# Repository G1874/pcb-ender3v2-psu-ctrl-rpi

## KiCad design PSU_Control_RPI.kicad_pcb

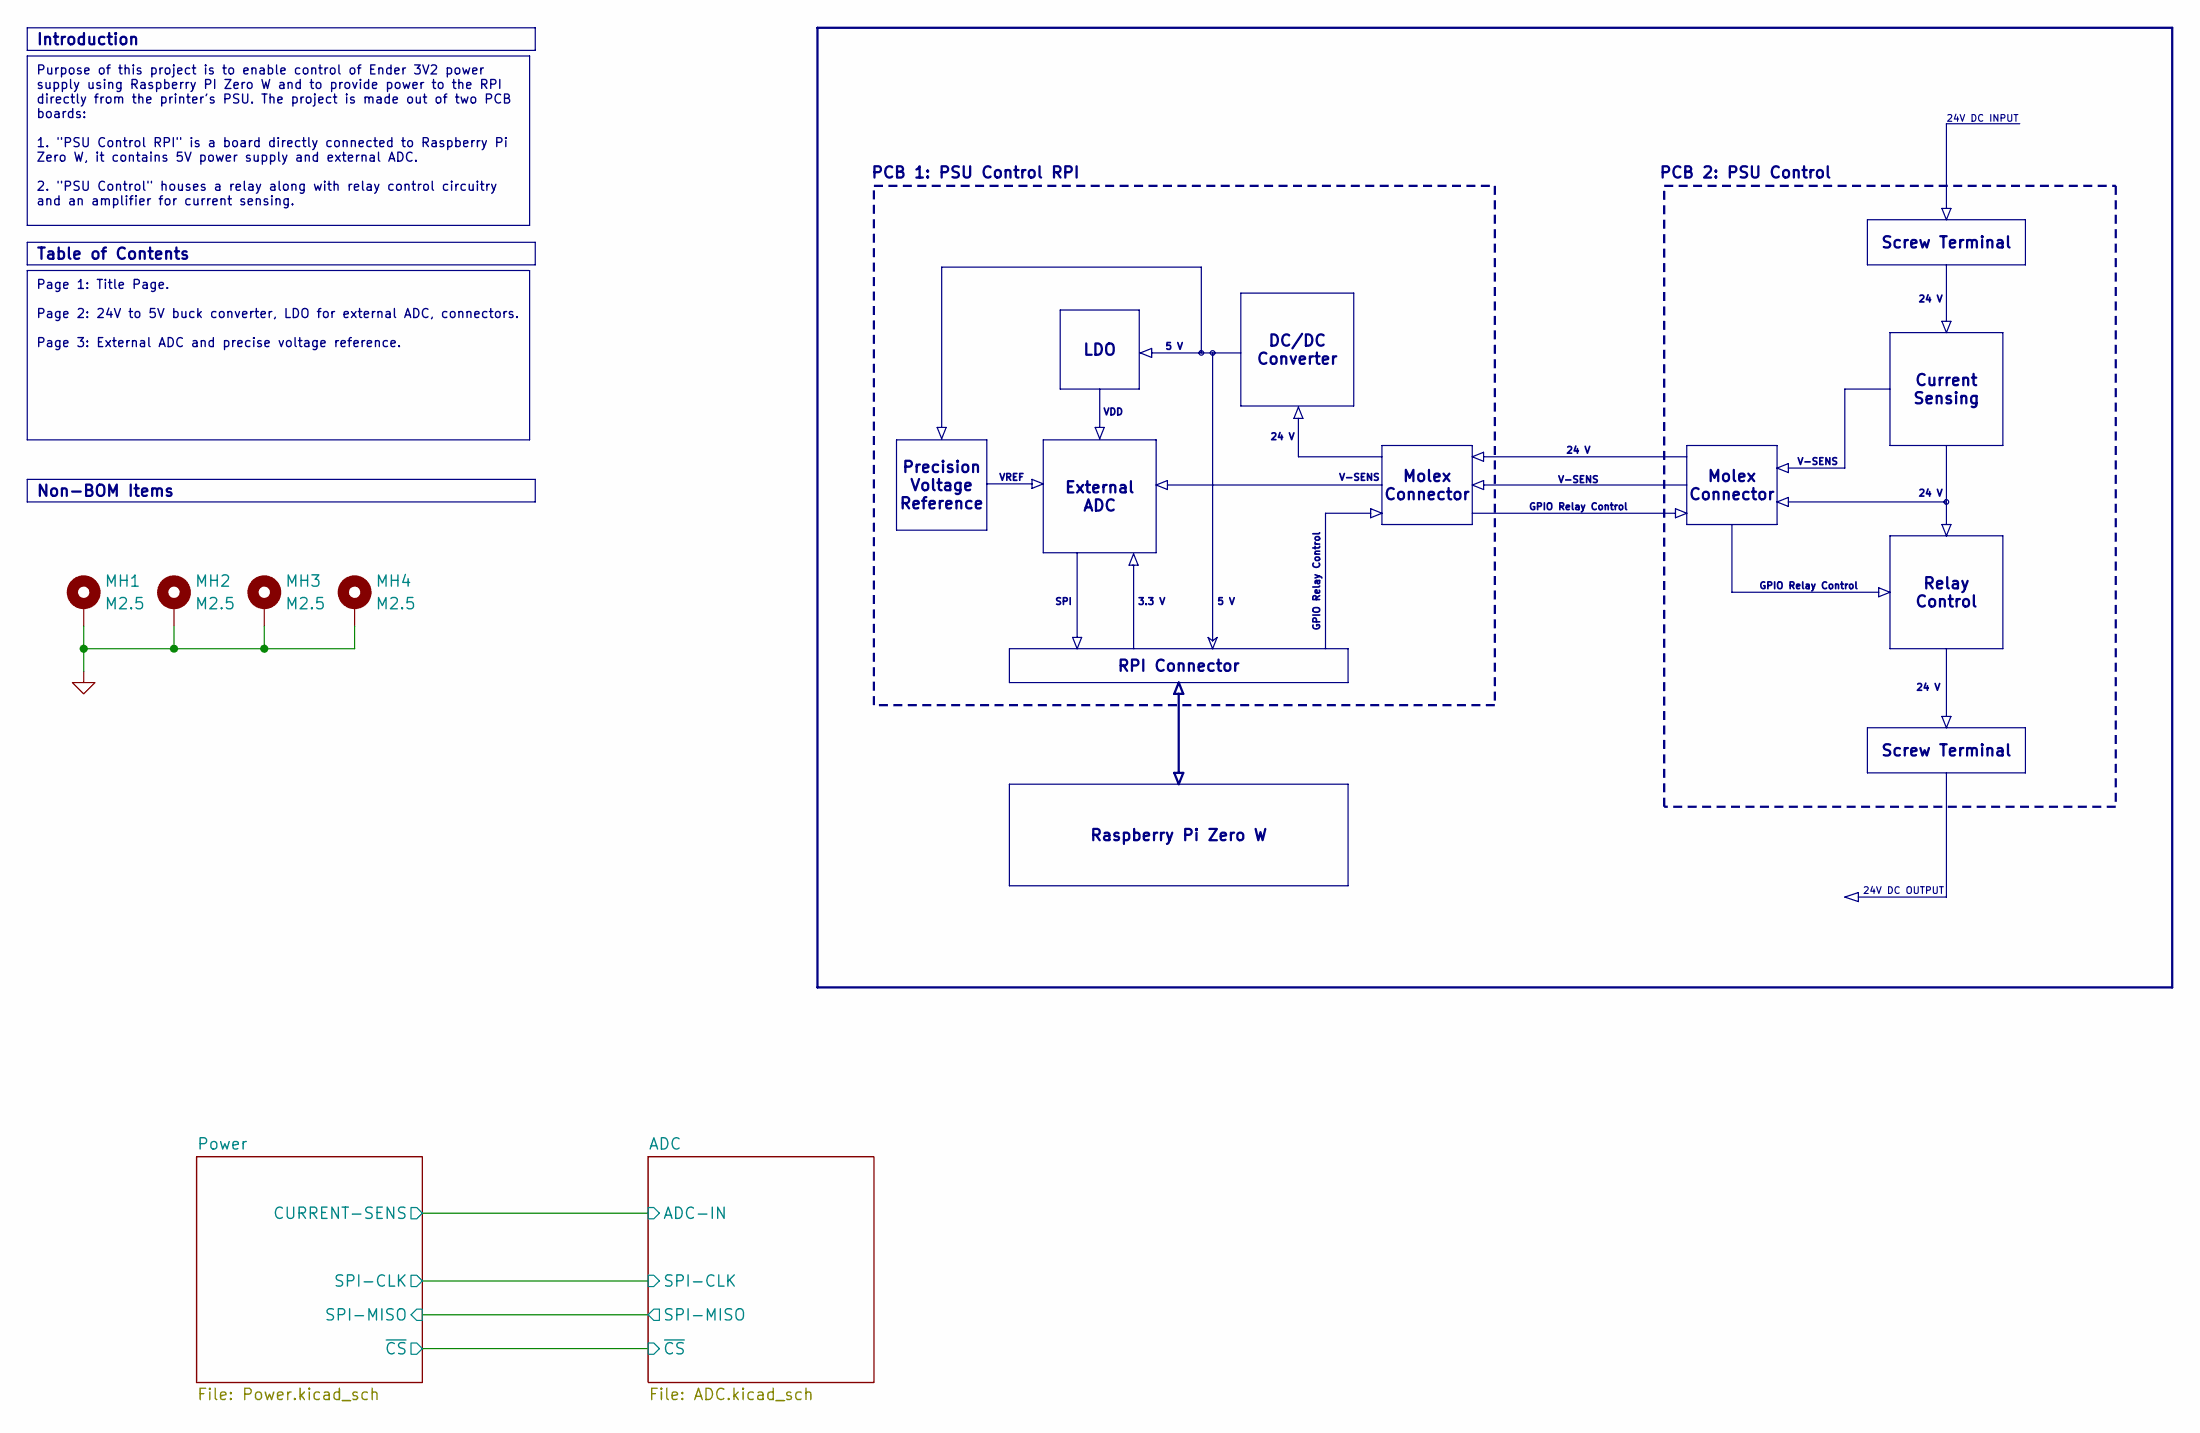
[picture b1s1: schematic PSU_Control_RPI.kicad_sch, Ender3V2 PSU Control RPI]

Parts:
MH1, MH2, MH3, MH4: M2.5; MountingHole_2.7mm_M2.5_ISO14580_Pad_TopOnly

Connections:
GND: MH1.1, MH2.1, MH3.1, MH4.1; also elsewhere on the board

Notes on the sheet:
24 V
PCB 1: PSU Control RPI
V-SENS
3.3 V
24V DC INPUT
GPIO Relay Control
SPI
VREF
VDD
5 V
PCB 2: PSU Control
24V DC OUTPUT
LDO
External ADC
Introduction
Molex Connector
Raspberry Pi Zero W
Screw Terminal
Relay Control
Non-BOM Items
Page 1: Title Page. Page 2: 24V to 5V buck converter, LDO for external ADC, connectors. Page 3: External ADC and precise voltage reference.
Current Sensing
Purpose of this project is to enable control of Ender 3V2 power supply using Raspberry PI Zero W and to provide power to the RPI directly from the printer's PSU. The project is made out of two PCB boards: 1. "PSU Control RPI" is a board directly connected to Raspberry Pi Zero W, it contains 5V powe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
Table of Contents
Precision Voltage Reference
RPI Connector
DC/DC Converter

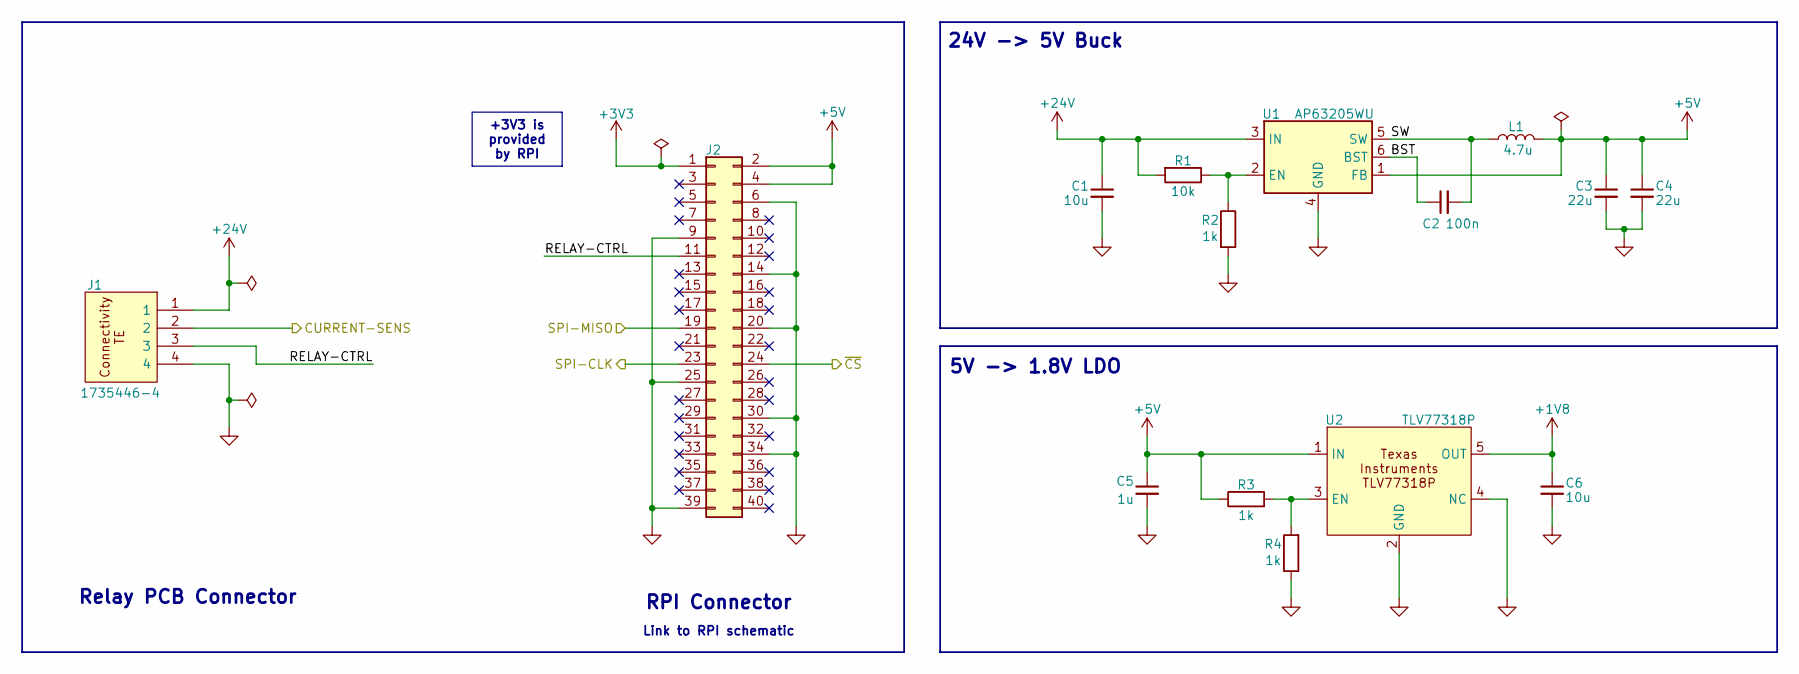
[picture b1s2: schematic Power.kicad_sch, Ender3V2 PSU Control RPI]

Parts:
C1, C6: 10u; C_1206_3216Metric_Pad1.33x1.80mm_HandSolder; Manufacturer Part Number CL31A106KBHNNNE
C2: 100n; C_0402_1005Metric_Pad0.74x0.62mm_HandSolder; Manufacturer Part Number GRM155R61H104KE19D
C3, C4: 22u; C_1206_3216Metric_Pad1.33x1.80mm_HandSolder; Manufacturer Part Number CL31A226KAHNNNE
C5: 1u; C_0603_1608Metric_Pad1.08x0.95mm_HandSolder; Manufacturer Part Number MCASL168SB7105KTNA01
J1: 1735446-4; SHDR4W60P0X200_1X4_1000X520X637P; Manufacturer Part Number 1735446-4
J2: 61304021821; Manufacturer Part Number 61304021821
L1: 4.7u; L_1008_2520Metric_Pad1.43x2.20mm_HandSolder; Manufacturer Part Number LCENA2520MKT4R7M0NK
R1: 10k; R_0603_1608Metric_Pad0.98x0.95mm_HandSolder; Manufacturer Part Number WCR-WCR0603LF-1002-F-P-LT
R2, R3, R4: 1k; R_0805_2012Metric_Pad1.20x1.40mm_HandSolder; Manufacturer Part Number ERA-6AEB102V
U1: AP63205WU; TSOT-23-6_HandSoldering; Manufacturer Part Number AP63205WU
U2: TLV77318P; SOT-23-5_HandSoldering; Manufacturer Part Number TLV77318P

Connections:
+1V8: C6.1, U2.5 (OUT); also elsewhere on the board
+3V3: J2.1; also elsewhere on the board
+5V: C3.1, C4.1, C5.1, J2.2, J2.4, L1.2, R3.1, U1.1 (FB), U2.1 (IN); also elsewhere on the board
+24V: C1.1, J1.1, R1.2, U1.3 (IN)
/ADC/ADC-IN: J1.2; also elsewhere on the board
/ADC/SPI-CLK: J2.23; also elsewhere on the board
/ADC/SPI-MISO: J2.19; also elsewhere on the board
/ADC/~CS: J2.24; also elsewhere on the board
/Power/BST: C2.1, U1.6 (BST)
/Power/RELAY-CTRL: J1.3, J2.11
/Power/SW: C2.2, L1.1, U1.5 (SW)
GND: C1.2, C3.2, C4.2, C5.2, C6.2, J1.4, J2.6, J2.9, J2.14, J2.20, J2.25, J2.30, J2.34, J2.39, R2.2, R4.1, U1.4 (GND), U2.2 (GND), U2.4 (NC); also elsewhere on the board
unnamed: R1.1, R2.1, U1.2 (EN)
unnamed: R3.2, R4.2, U2.3 (EN)

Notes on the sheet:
RPI Connector
Relay PCB Connector
24V -> 5V Buck
Link to RPI schematic
5V -> 1.8V LDO
+3V3 is provided by RPI

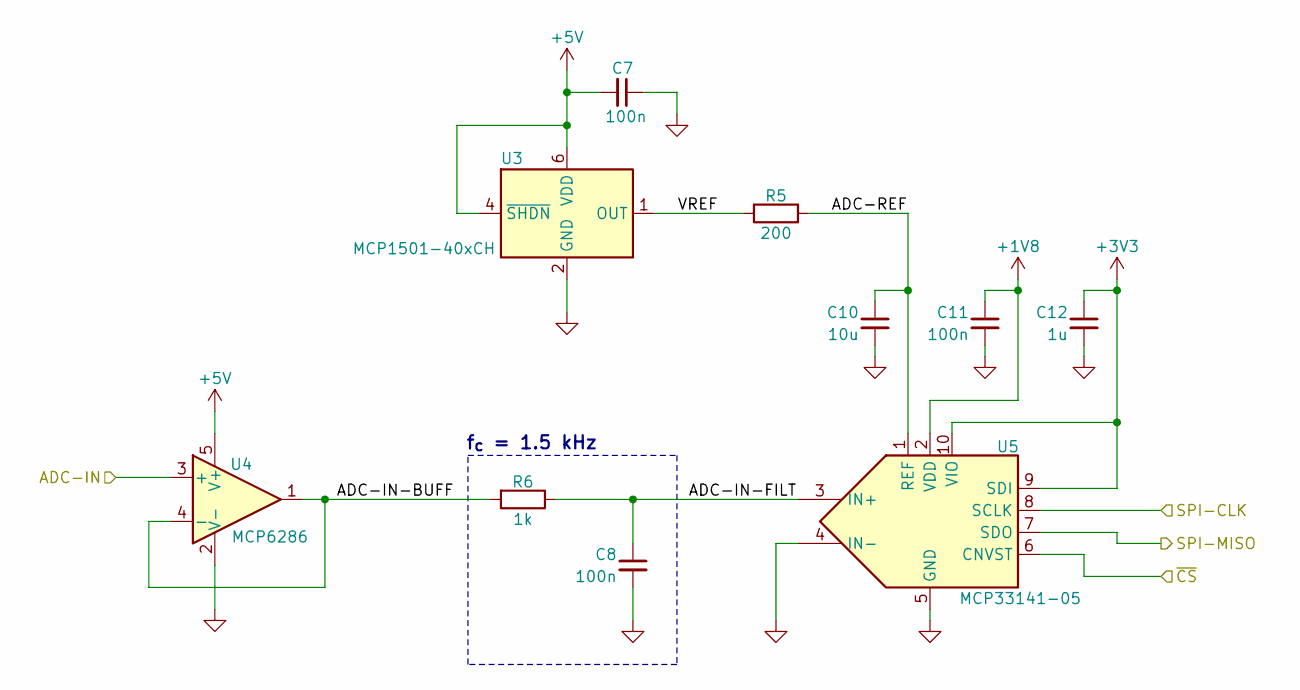
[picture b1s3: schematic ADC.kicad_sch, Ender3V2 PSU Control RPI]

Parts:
C7, C8, C11: 100n; C_0402_1005Metric_Pad0.74x0.62mm_HandSolder; Manufacturer Part Number GRM155R61H104KE19D
C10: 10u; C_0603_1608Metric_Pad1.08x0.95mm_HandSolder; Manufacturer Part Number TCM1A106M8R
C12: 1u; C_0603_1608Metric_Pad1.08x0.95mm_HandSolder; Manufacturer Part Number MCASL168SB7105KTNA01
R5: 200; R_0603_1608Metric_Pad0.98x0.95mm_HandSolder; Manufacturer Part Number ERA-3AEB201V
R6: 1k; R_0805_2012Metric_Pad1.20x1.40mm_HandSolder; Manufacturer Part Number ERA-6AEB102V
U3: MCP1501-40xCH; SOT-23-6_Handsoldering; Manufacturer Part Number MCP1501T-40E/CHY
U4: MCP6286; SOT-23-5_HandSoldering; Manufacturer Part Number MCP6286
U5: MCP33141-05; MSOP-10; Manufacturer Part Number MCP33141-05

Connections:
+1V8: C11.1, U5.2 (VDD); also elsewhere on the board
+3V3: C12.1, U5.9 (SDI), U5.10 (VIO); also elsewhere on the board
+5V: C7.2, U3.4 (~SHDN), U3.6 (VDD), U4.5 (V+); also elsewhere on the board
/ADC/ADC-IN: U4.3 (+); also elsewhere on the board
/ADC/ADC-IN-BUFF: R6.2, U4.1, U4.4 (-)
/ADC/ADC-IN-FILT: C8.1, R6.1, U5.3 (IN+)
/ADC/ADC-REF: C10.1, R5.2, U5.1 (REF)
/ADC/SPI-CLK: U5.8 (SCLK); also elsewhere on the board
/ADC/SPI-MISO: U5.7 (SDO); also elsewhere on the board
/ADC/VREF: R5.1, U3.1 (OUT)
/ADC/~CS: U5.6 (CNVST); also elsewhere on the board
GND: C7.1, C8.2, C10.2, C11.2, C12.2, U3.2 (GND), U3.3 (GND), U3.5 (GND), U4.2 (V-), U5.4 (IN-), U5.5 (GND); also elsewhere on the board

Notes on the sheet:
f_{c} = 1.5 kHz

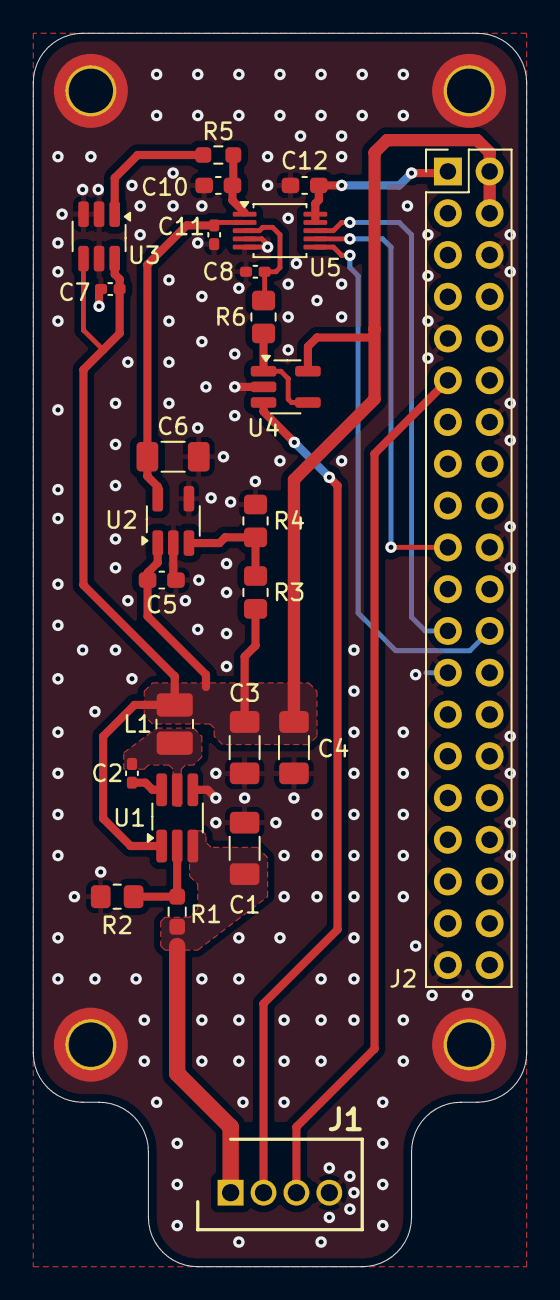
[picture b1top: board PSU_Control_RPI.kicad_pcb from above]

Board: 2 copper layers, 30.0 x 75.0 mm, 29 parts (0 on the bottom side), 18 nets.
